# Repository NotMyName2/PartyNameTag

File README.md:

# PartyNameTag

Remember the nasty sticky paper name tags probably used at parties? Never been to any party, so I do not. Anyway, once I figure out how to put this thingy on a shirt, it can be used as a name tag.

The device can display any reasonably long message consisting of the characters in the English alphabet sent by Bluetooth from any smartphone(tested only on android). The text shifts in the same way like a "breaking news" row in the news.

In the future, I might add more functionality:

 	 *display a hard-coded message after a certain period of inactivity
        (You can ask for a girl's number this way :O )

  	*display random noise(partially done)

  	*up- and down-shifting

  	*finish the character lookup table

  	*implement the LED indicator for low battery

  	*display special emoji or animations

The thingy is based on Arduino Pro Mini, an AT09 Bluetooth module, a TC4056 Li-ion charger module, an old phone battery, 74HC595 shift registers, a DC-DC 5V voltage supply and many unipolar transistors.

The microcontroller can be easily reprogrammed using the Arduino IDE and a USB to Serial converter.

The custom PCB is in the "DivineMessengerBoard" directory. The smallest track width is 0.4mm and the smallest clearance is 0.2mm and is meant to be manufactured professionally (DIY drill or UV would probably bring frustration)

See the video at https://youtu.be/IolG6l6WMoY

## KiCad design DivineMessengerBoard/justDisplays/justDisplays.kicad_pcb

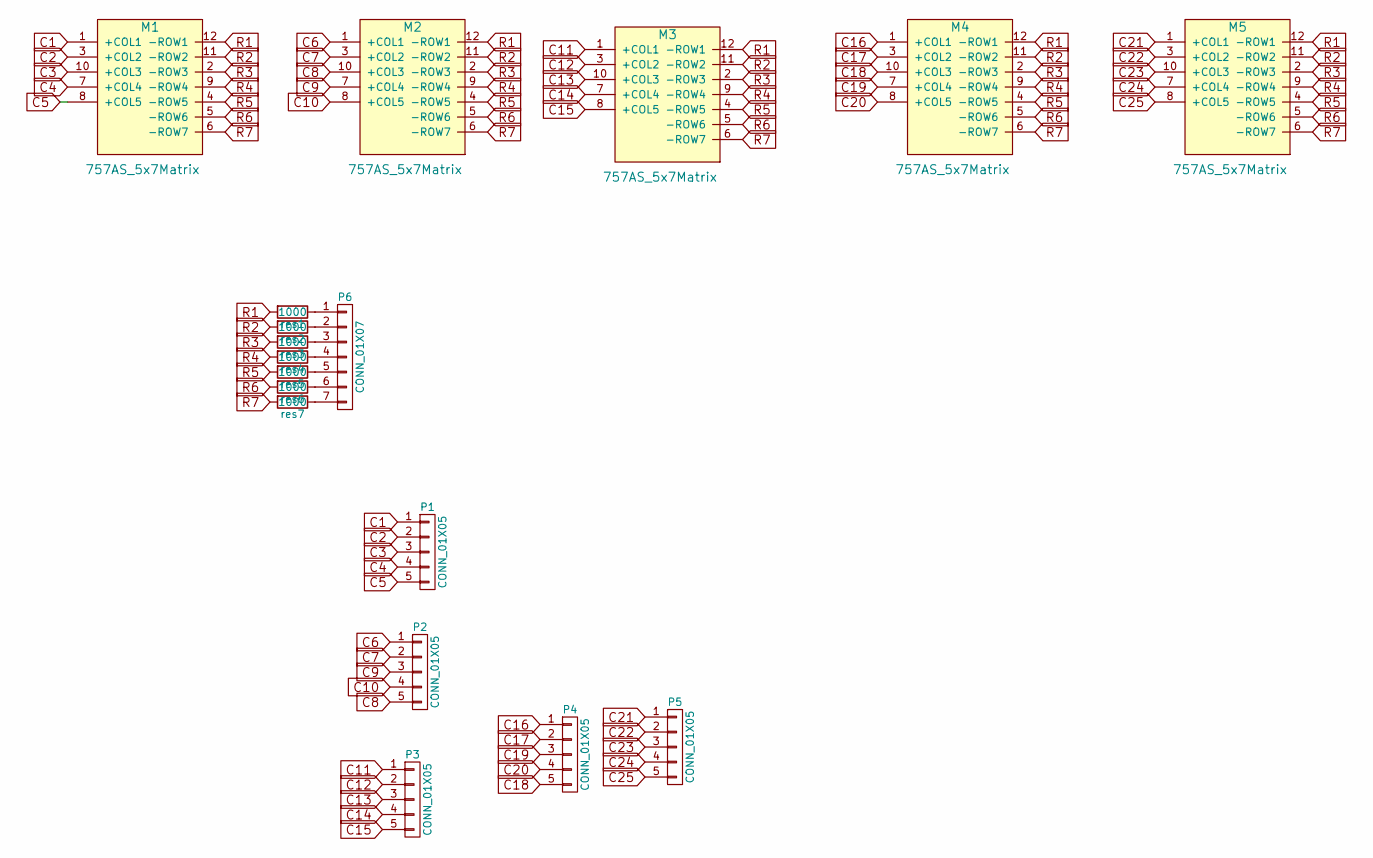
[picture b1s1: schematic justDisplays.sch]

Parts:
M1, M2, M3, M4, M5: 757AS_5x7Matrix; 757-5x7Matrix-socket
P1, P2, P3, P4, P5: CONN_01X05; NonRetardHeader1x5
P6: CONN_01X07; NonRetardHeader1x7
res1, res2, res3, res4, res5, res6, res7: 1000; R_1206_HandSoldering

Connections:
C1: M1.1 (+COL1), P1.1
C2: M1.3 (+COL2), P1.2
C3: M1.10 (+COL3), P1.3
C4: M1.7 (+COL4), P1.4
C5: M1.8 (+COL5), P1.5
C6: M2.1 (+COL1), P2.1
C7: M2.3 (+COL2), P2.2
C8: M2.10 (+COL3), P2.5
C9: M2.7 (+COL4), P2.3
C10: M2.8 (+COL5), P2.4
C11: M3.1 (+COL1), P3.1
C12: M3.3 (+COL2), P3.2
C13: M3.10 (+COL3), P3.3
C14: M3.7 (+COL4), P3.4
C15: M3.8 (+COL5), P3.5
C16: M4.1 (+COL1), P4.1
C17: M4.3 (+COL2), P4.2
C18: M4.10 (+COL3), P4.5
C19: M4.7 (+COL4), P4.3
C20: M4.8 (+COL5), P4.4
C21: M5.1 (+COL1), P5.1
C22: M5.3 (+COL2), P5.2
C23: M5.10 (+COL3), P5.3
C24: M5.7 (+COL4), P5.4
C25: M5.8 (+COL5), P5.5
unnamed: P6.1, res1.1
unnamed: P6.2, res2.1
unnamed: P6.3, res3.1
unnamed: P6.4, res4.1
unnamed: P6.5, res5.1
unnamed: P6.6, res6.1
unnamed: P6.7, res7.1
R1: M1.12 (-ROW1), M2.12 (-ROW1), M3.12 (-ROW1), M4.12 (-ROW1), M5.12 (-ROW1), res1.2
R2: M1.11 (-ROW2), M2.11 (-ROW2), M3.11 (-ROW2), M4.11 (-ROW2), M5.11 (-ROW2), res2.2
R3: M1.2 (-ROW3), M2.2 (-ROW3), M3.2 (-ROW3), M4.2 (-ROW3), M5.2 (-ROW3), res3.2
R4: M1.9 (-ROW4), M2.9 (-ROW4), M3.9 (-ROW4), M4.9 (-ROW4), M5.9 (-ROW4), res4.2
R5: M1.4 (-ROW5), M2.4 (-ROW5), M3.4 (-ROW5), M4.4 (-ROW5), M5.4 (-ROW5), res5.2
R6: M1.5 (-ROW6), M2.5 (-ROW6), M3.5 (-ROW6), M4.5 (-ROW6), M5.5 (-ROW6), res6.2
R7: M1.6 (-ROW7), M2.6 (-ROW7), M3.6 (-ROW7), M4.6 (-ROW7), M5.6 (-ROW7), res7.2

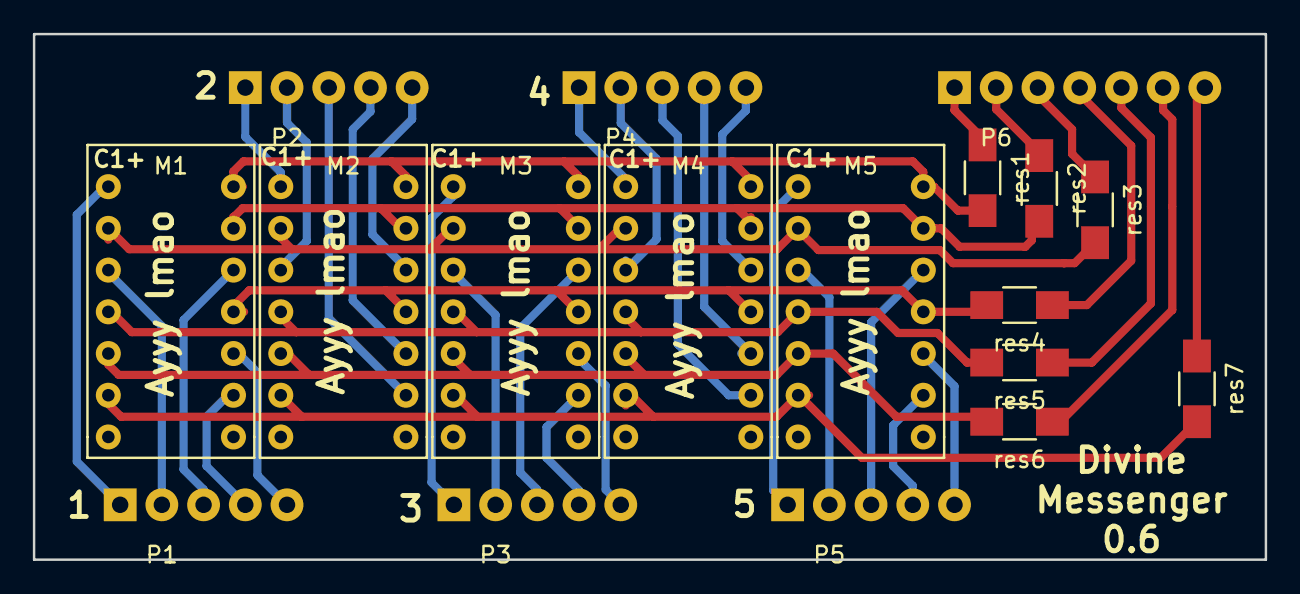
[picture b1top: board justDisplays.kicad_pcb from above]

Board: 2 copper layers, 75.0 x 32.0 mm, 18 parts (0 on the bottom side), 39 nets.

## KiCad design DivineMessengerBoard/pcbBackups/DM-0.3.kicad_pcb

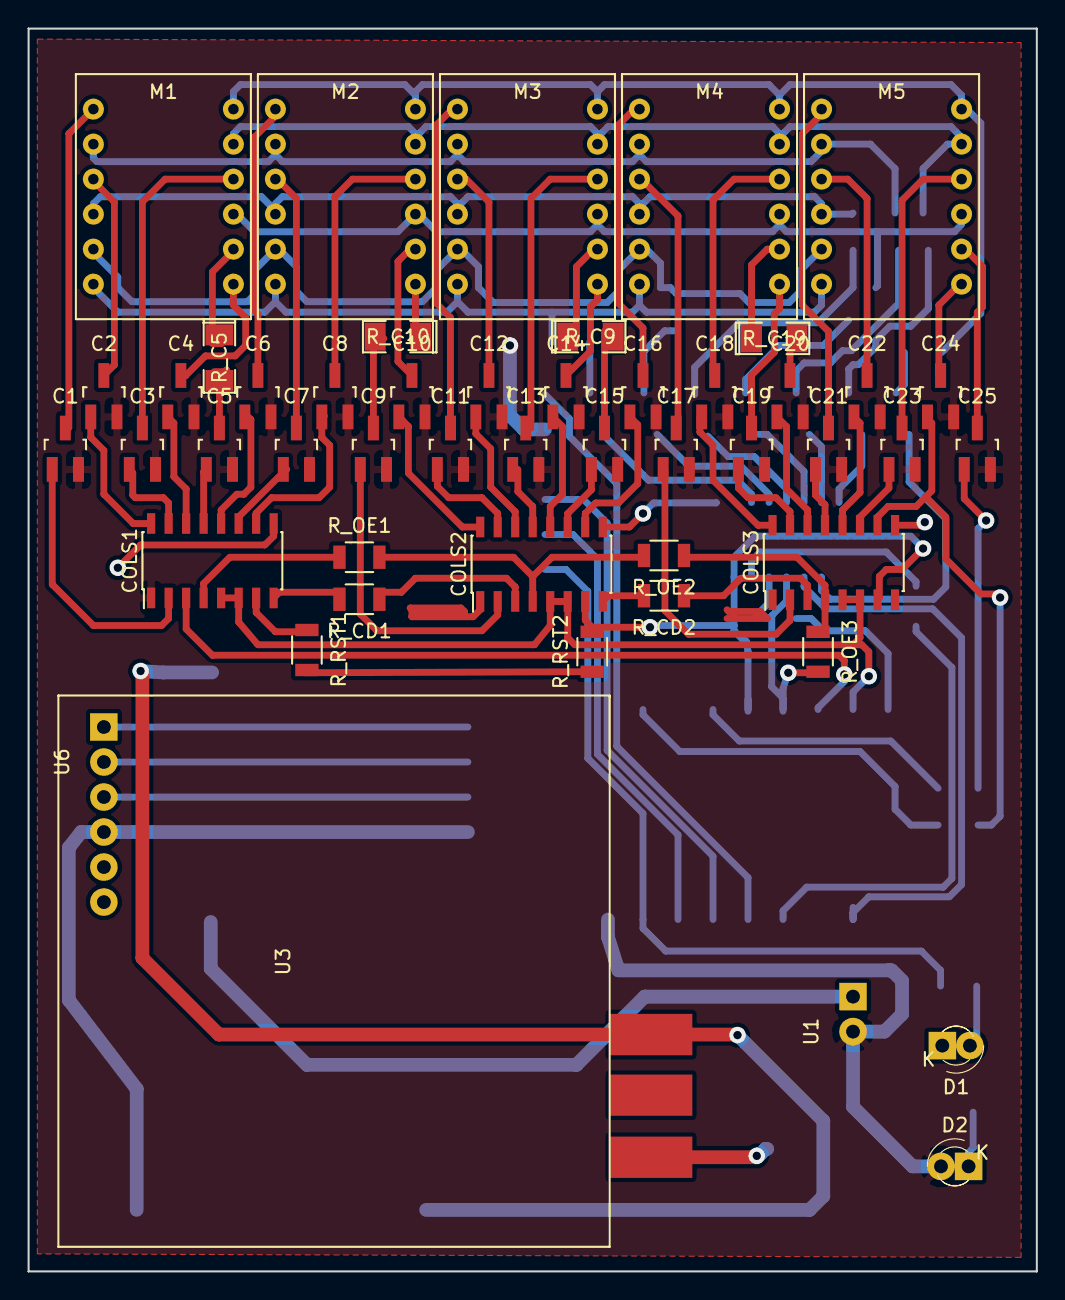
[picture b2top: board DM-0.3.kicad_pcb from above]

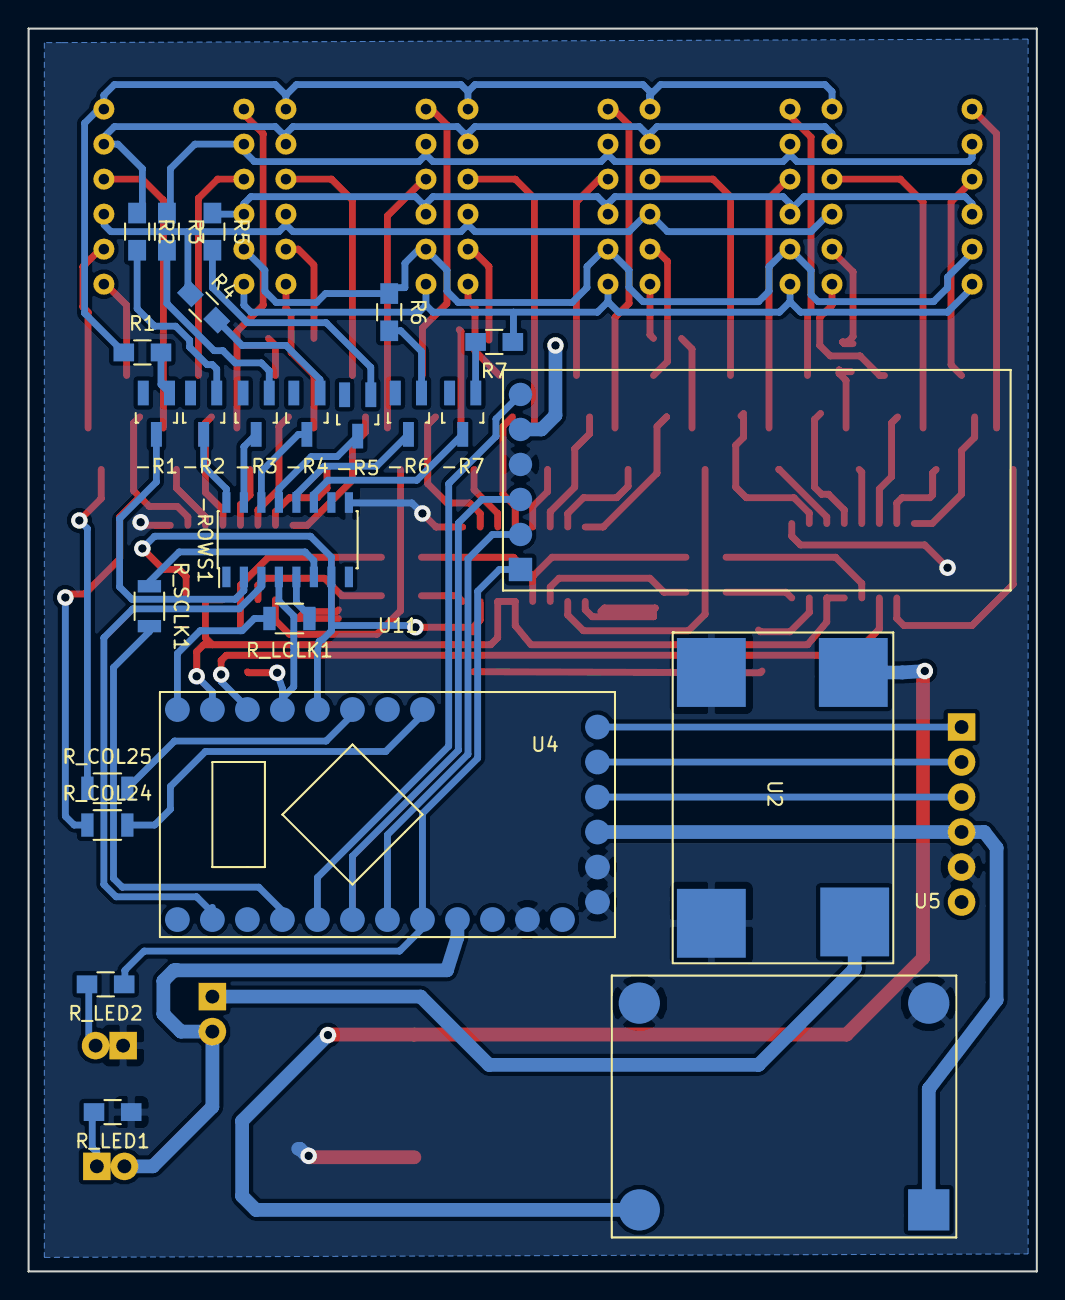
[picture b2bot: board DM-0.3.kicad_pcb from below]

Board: 2 copper layers, 73.2 x 90.2 mm, 74 parts (25 on the bottom side), 109 nets.

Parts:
-R1, -R2, -R3, -R4, -R5, -R6, -R7: Q_NMOS_DSG; SOT-23_Handsoldering
-ROWS1: 74HC595-F; SOIC-16_3.9x9.9mm_Pitch1.27mm
C1, C2, C3, C4, C5, C6, C7, C8, C9, C10, C11, C12, C13, C14, C15, C16, C17, C18, C19, C20, C21, C22, C23, C24, C25: Q_PMOS_GDS; SOT-23_Handsoldering
COLS1, COLS2, COLS3: 74HC595-F; SOIC-16_3.9x9.9mm_Pitch1.27mm
D1, D2: Led_Small; LED-3MM
M1, M2, M3, M4, M5: 757AS_5x7Matrix; 757-5x7Matrix
R1, R2, R3, R4, R5, R6, R7: 220; R_0805_HandSoldering
R_C5, R_C9, R_C10, R_C19: 0; SMD-1206_Pol
R_CD1, R_CD2: 0; R_1206
R_COL24, R_COL25: 0; R_1206
R_LCLK1: 0; R_1206
R_LED1, R_LED2: 220; R_0805_HandSoldering
R_OE1, R_OE2, R_OE3: 0; R_1206
R_RST1, R_RST2: 0; R_1206
R_SCLK1: 0; R_1206
U1: NonRetardHeader1x2
U2: DC-DC
U3: OldBat; DC-DC
U4: ArProMin; ProMiniSMDNoWeirdAndRxTxPins
U5: Li-Ion_Charger; Li-Ion-charger2-SMD
U6: NonRetardHeader; NonRetardHeader1x6
U11: BTModule; BtModuleSMD

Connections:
5V: C1.2, C2.2, C3.2, C4.2, C5.2, C6.2, C7.2, C8.2, C9.2, C10.2, C11.2, C12.2, C13.2, C14.2, C15.2, C16.2, C17.2, C18.2, C19.2, C20.2, C21.2, C22.2, C23.2, C24.2, C25.2, COLS1.1, D2.2, U1.2, U4.24, U11.5
BAT+: U2.1, U3.1, U5.4
BTIN: U4.22, U11.2
BTOUT: U4.21, U11.3
BT_CON: R_LED2.1, U4.23, U11.1
BT_EN: U4.20, U11.6
C1: C1.3, M1.1
C2: C2.3, M1.3
C3: C3.3, M1.10
C4: C4.3, M1.7
C5: C5.3, R_C5.2
C6: C6.3, M2.1
C7: C7.3, M2.3
C8: C8.3, M2.10
C9: C9.3, R_C10.2
C10: C10.3, M2.8
C11: C11.3, M3.1
C12: C12.3, M3.3
C13: C13.3, M3.10
C14: C14.3, M3.7
C15: C15.3, R_C9.2
C16: C16.3, M4.1
C17: C17.3, M4.3
C18: C18.3, M4.10
C19: C19.3, M4.7
C20: C20.3, R_C19.2
C21: C21.3, M5.1
C22: C22.3, M5.3
C23: C23.3, M5.10
C24: C24.3, M5.7
C25: C25.3, M5.8
CHRGR: U4.30, U5.1, U6.4
COL1: C1.1, COLS1.2
COL2: C2.1, COLS1.16
COL3: C3.1, COLS1.15
COL4: C4.1, COLS1.14
COL5: C5.1, COLS1.13
COL6: C6.1, COLS1.12
COL7: C7.1, COLS1.11
COL8: C8.1, COLS1.10
COL9: C9.1, COLS2.2
COL10: C10.1, COLS2.16
COL11: C11.1, COLS2.15
COL12: C12.1, COLS2.14
COL13: C13.1, COLS2.13
COL14: C14.1, COLS2.12
COL15: C15.1, COLS2.11
COL16: C16.1, COLS2.10
COL17: C17.1, COLS3.2
COL18: C18.1, COLS3.16
COL19: C19.1, COLS3.15
COL20: C20.1, COLS3.14
COL21: C21.1, COLS3.13
COL22: C22.1, COLS3.12
COL23: C23.1, COLS3.11
COL24: C24.1, COLS3.10, R_COL24.1
COL25: C25.1, R_COL25.1
ColClk: COLS1.5, COLS1.6, COLS2.5, COLS2.6, COLS3.5, COLS3.6, U4.11
ColIn: COLS1.3, U4.10
GND: -ROWS1.9, COLS1.9, COLS2.9, COLS3.9, D1.1, R_LED1.1, U2.2, U2.3, U3.3, U4.26, U4.28, U4.29, U5.2, U5.3, U6.5, U11.4
unnamed: -R1.1, R1.2
unnamed: -R2.1, R2.2
unnamed: -R3.1, R3.2
unnamed: -R4.1, R4.2
unnamed: -R5.1, R5.2
unnamed: -R6.1, R6.2
unnamed: -R7.1, R7.2
unnamed: -ROWS1.5, R_LCLK1.1
unnamed: -ROWS1.6, R_SCLK1.1
unnamed: COLS1.4, R_OE1.1
unnamed: COLS1.7, R_RST1.1
unnamed: COLS1.8, R_CD1.2
unnamed: COLS2.3, R_CD1.1
unnamed: COLS2.4, R_OE1.2, R_OE2.2
unnamed: COLS2.8, R_CD2.2
unnamed: COLS3.3, R_CD2.1
unnamed: COLS3.4, R_OE2.1, R_OE3.1
unnamed: D1.2, R_LED2.2
unnamed: D2.1, R_LED1.2
unnamed: M1.8, R_C5.1
unnamed: M2.7, R_C10.1
unnamed: M3.8, R_C9.1
unnamed: M4.8, R_C19.1
unnamed: R_COL24.2, U4.5
unnamed: R_COL25.2, U4.7
unnamed: R_RST1.2, R_RST2.1
unnamed: U4.33, U6.1
unnamed: U4.31, U6.3
unnamed: U4.32, U6.2
OE: -ROWS1.4, R_OE3.2, U4.9
Pow: U1.1, U2.4
R1: M1.12, M2.12, M3.12, M4.12, M5.12, R1.1
R2: M1.11, M2.11, M3.11, M4.11, M5.11, R2.1
R3: M1.2, M2.2, M3.2, M4.2, M5.2, R3.1
R4: M1.9, M2.9, M3.9, M4.9, M5.9, R4.1
R5: M1.4, M2.4, M3.4, M4.4, M5.4, R5.1
R6: M1.5, M2.5, M3.5, M4.5, M5.5, R6.1
R7: M1.6, M2.6, M3.6, M4.6, M5.6, R7.1
ROW1: -R1.3, -ROWS1.2
ROW2: -R2.3, -ROWS1.16
ROW3: -R3.3, -ROWS1.15
ROW4: -R4.3, -ROWS1.14
ROW5: -R5.3, -ROWS1.13
ROW6: -R6.3, -ROWS1.12
ROW7: -R7.3, -ROWS1.11
RST: -ROWS1.7, COLS2.7, COLS3.7, R_RST2.2, U4.8
RowIn: -ROWS1.3, U4.17
RowLClk: R_LCLK1.2, U4.12
RowSClk: R_SCLK1.2, U4.19

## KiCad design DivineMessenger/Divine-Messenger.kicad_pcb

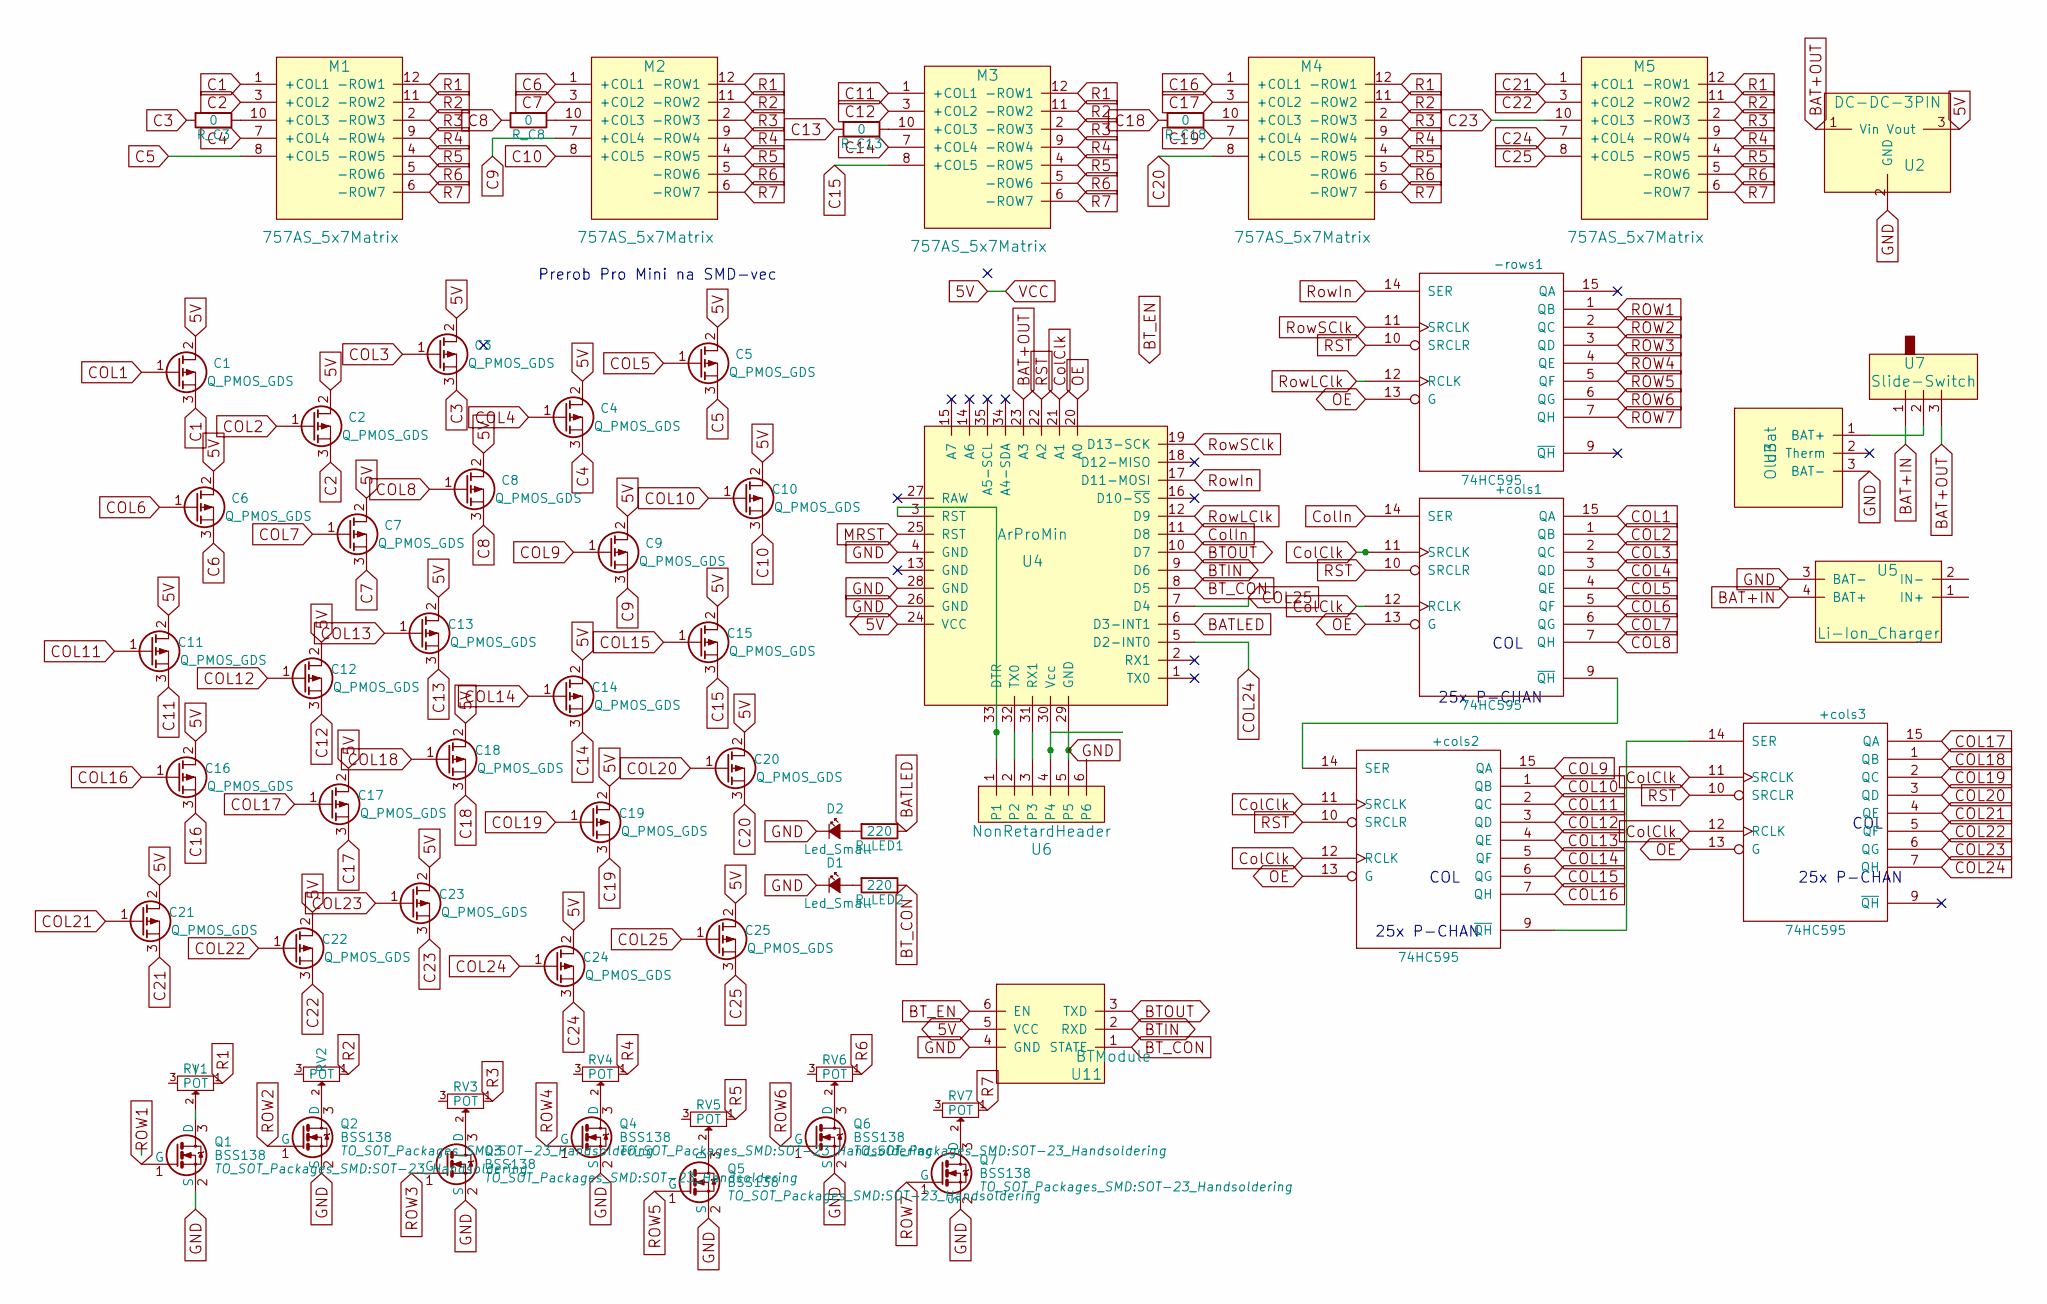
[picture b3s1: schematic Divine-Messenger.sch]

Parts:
+cols1, +cols2, +cols3: 74HC595; SOIC-16_3.9x9.9mm_Pitch1.27mm
-rows1: 74HC595; SOIC-16_3.9x9.9mm_Pitch1.27mm
C1, C2, C3, C4, C5, C6, C7, C8, C9, C10, C11, C12, C13, C14, C15, C16, C17, C18, C19, C20, C21, C22, C23, C24, C25: Q_PMOS_GDS; SOT-23_Handsoldering
D1, D2: Led_Small; LED-3MM
M1, M2, M3, M4, M5: 757AS_5x7Matrix; 757-5x7Matrix
Q1, Q2, Q3, Q4, Q5, Q6, Q7: BSS138; SOT-23_Handsoldering
RV1, RV2, RV3, RV4, RV5, RV6, RV7: POT; SMD-Trimm
R_C3, R_C8, R_C13, R_C18: 0; R_1206_HandSoldering
R_LED1, R_LED2: 220; R_0805_HandSoldering
U2: DC-DC-3PIN; NonRetardHeader1x3
U3: OldBat; oldBatTHT
U4: ArProMin; ProMiniSMDNoWeirdAndRxTxPinsLongPads
U5: Li-Ion_Charger; Li-Ion-charger1-SMD-LongPads
U6: NonRetardHeader; NonRetardHeader1x6
U7: Slide-Switch
U11: BTModule; BtModuleSMDLongPads

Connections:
5V: -rows1.16 (VCC), C1.2 (D), C2.2 (D), C3.2 (D), C4.2 (D), C5.2 (D), C6.2 (D), C7.2 (D), C8.2 (D), C9.2 (D), C10.2 (D), C11.2 (D), C12.2 (D), C13.2 (D), C14.2 (D), C15.2 (D), C16.2 (D), C17.2 (D), C18.2 (D), C19.2 (D), C20.2 (D), C21.2 (D), C22.2 (D), C23.2 (D), C24.2 (D), C25.2 (D), U2.3 (Vout), U4.24 (VCC), U11.5 (VCC); also elsewhere on the board
BAT+IN: U5.4 (BAT+), U7.1
BAT+OUT: U2.1 (Vin), U4.23 (A3), U7.3
BATLED: R_LED1.1, U4.6 (D3-INT1)
BTIN: U4.9 (D6), U11.2 (RXD)
BTOUT: U4.10 (D7), U11.3 (TXD)
BT_CON: R_LED2.1, U4.8 (D5), U11.1 (STATE)
C1: C1.3 (S), M1.1 (+COL1)
C2: C2.3 (S), M1.3 (+COL2)
C3: C3.3 (S), R_C3.2
C4: C4.3 (S), M1.7 (+COL4)
C5: C5.3 (S), M1.8 (+COL5)
C6: C6.3 (S), M2.1 (+COL1)
C7: C7.3 (S), M2.3 (+COL2)
C8: C8.3 (S), R_C8.2
C9: C9.3 (S), M2.7 (+COL4)
C10: C10.3 (S), M2.8 (+COL5)
C11: C11.3 (S), M3.1 (+COL1)
C12: C12.3 (S), M3.3 (+COL2)
C13: C13.3 (S), R_C13.2
C14: C14.3 (S), M3.7 (+COL4)
C15: C15.3 (S), M3.8 (+COL5)
C16: C16.3 (S), M4.1 (+COL1)
C17: C17.3 (S), M4.3 (+COL2)
C18: C18.3 (S), R_C18.2
C19: C19.3 (S), M4.7 (+COL4)
C20: C20.3 (S), M4.8 (+COL5)
C21: C21.3 (S), M5.1 (+COL1)
C22: C22.3 (S), M5.3 (+COL2)
C23: C23.3 (S), M5.10 (+COL3)
C24: C24.3 (S), M5.7 (+COL4)
C25: C25.3 (S), M5.8 (+COL5)
COL1: +cols1.15 (QA), C1.1 (G); also elsewhere on the board
COL2: +cols1.1 (QB), C2.1 (G); also elsewhere on the board
COL3: +cols1.2 (QC), C3.1 (G); also elsewhere on the board
COL4: +cols1.3 (QD), C4.1 (G); also elsewhere on the board
COL5: +cols1.4 (QE), C5.1 (G); also elsewhere on the board
COL6: +cols1.5 (QF), C6.1 (G); also elsewhere on the board
COL7: +cols1.6 (QG), C7.1 (G); also elsewhere on the board
COL8: +cols1.7 (QH), C8.1 (G); also elsewhere on the board
COL9: +cols2.15 (QA), C9.1 (G); also elsewhere on the board
COL10: +cols2.1 (QB), C10.1 (G); also elsewhere on the board
COL11: +cols2.2 (QC), C11.1 (G); also elsewhere on the board
COL12: +cols2.3 (QD), C12.1 (G); also elsewhere on the board
COL13: +cols2.4 (QE), C13.1 (G); also elsewhere on the board
COL14: +cols2.5 (QF), C14.1 (G); also elsewhere on the board
COL15: +cols2.6 (QG), C15.1 (G); also elsewhere on the board
COL16: +cols2.7 (QH), C16.1 (G); also elsewhere on the board
COL17: +cols3.15 (QA), C17.1 (G); also elsewhere on the board
COL18: +cols3.1 (QB), C18.1 (G); also elsewhere on the board
COL19: +cols3.2 (QC), C19.1 (G); also elsewhere on the board
COL20: +cols3.3 (QD), C20.1 (G); also elsewhere on the board
COL21: +cols3.4 (QE), C21.1 (G); also elsewhere on the board
COL22: +cols3.5 (QF), C22.1 (G); also elsewhere on the board
COL23: +cols3.6 (QG), C23.1 (G); also elsewhere on the board
COL24: +cols3.7 (QH), C24.1 (G), U4.5 (D2-INT0); also elsewhere on the board
COL25: C25.1 (G), U4.7 (D4)
ColClk: +cols1.11 (SRCLK), +cols1.12 (RCLK), +cols2.11 (SRCLK), +cols2.12 (RCLK), +cols3.11 (SRCLK), +cols3.12 (RCLK), U4.21 (A1); also elsewhere on the board
ColIn: +cols1.14 (SER), U4.11 (D8); also elsewhere on the board
GND: -rows1.8 (GND), D1.1 (K), D2.1 (K), Q1.2 (S), Q2.2 (S), Q3.2 (S), Q4.2 (S), Q5.2 (S), Q6.2 (S), Q7.2 (S), U2.2 (GND), U3.3 (BAT-), U4.4 (GND), U4.26 (GND), U4.28 (GND), U4.29 (GND), U5.3 (BAT-), U6.5, U11.4 (GND); also elsewhere on the board
unnamed 60: +cols1.9 (~QH), +cols2.14 (SER); also elsewhere on the board
unnamed 61: +cols2.9 (~QH), +cols3.14 (SER); also elsewhere on the board
unnamed: D1.2 (A), R_LED2.2
unnamed: D2.2 (A), R_LED1.2
unnamed: M1.10 (+COL3), R_C3.1
unnamed: M2.10 (+COL3), R_C8.1
unnamed: M3.10 (+COL3), R_C13.1
unnamed: M4.10 (+COL3), R_C18.1
unnamed: Q1.3 (D), RV1.2
unnamed: Q2.3 (D), RV2.2
unnamed: Q3.3 (D), RV3.2
unnamed: Q4.3 (D), RV4.2
unnamed: Q5.3 (D), RV5.2
unnamed: Q6.3 (D), RV6.2
unnamed: Q7.3 (D), RV7.2
unnamed: U3.1 (BAT+), U7.2
unnamed: U4.3 (RST), U4.33 (DTR), U6.1
unnamed: U4.30 (Vcc), U6.4
unnamed: U4.31 (RX1), U6.3
unnamed: U4.32 (TX0), U6.2
OE: +cols1.13 (G), +cols2.13 (G), +cols3.13 (G), -rows1.13 (G), U4.20 (A0); also elsewhere on the board
R1: M1.12 (-ROW1), M2.12 (-ROW1), M3.12 (-ROW1), M4.12 (-ROW1), M5.12 (-ROW1), RV1.1
R2: M1.11 (-ROW2), M2.11 (-ROW2), M3.11 (-ROW2), M4.11 (-ROW2), M5.11 (-ROW2), RV2.1
R3: M1.2 (-ROW3), M2.2 (-ROW3), M3.2 (-ROW3), M4.2 (-ROW3), M5.2 (-ROW3), RV3.1
R4: M1.9 (-ROW4), M2.9 (-ROW4), M3.9 (-ROW4), M4.9 (-ROW4), M5.9 (-ROW4), RV4.1
R5: M1.4 (-ROW5), M2.4 (-ROW5), M3.4 (-ROW5), M4.4 (-ROW5), M5.4 (-ROW5), RV5.1
R6: M1.5 (-ROW6), M2.5 (-ROW6), M3.5 (-ROW6), M4.5 (-ROW6), M5.5 (-ROW6), RV6.1
R7: M1.6 (-ROW7), M2.6 (-ROW7), M3.6 (-ROW7), M4.6 (-ROW7), M5.6 (-ROW7), RV7.1
ROW1: -rows1.1 (QB), Q1.1 (G)
ROW2: -rows1.2 (QC), Q2.1 (G)
ROW3: -rows1.3 (QD), Q3.1 (G)
ROW4: -rows1.4 (QE), Q4.1 (G)
ROW5: -rows1.5 (QF), Q5.1 (G)
ROW6: -rows1.6 (QG), Q6.1 (G)
ROW7: -rows1.7 (QH), Q7.1 (G)
RST: +cols1.10 (SRCLR), +cols2.10 (SRCLR), +cols3.10 (SRCLR), -rows1.10 (SRCLR), U4.22 (A2); also elsewhere on the board
RowIn: -rows1.14 (SER), U4.17 (D11-MOSI)
RowLClk: -rows1.12 (RCLK), U4.12 (D9)
RowSClk: -rows1.11 (SRCLK), U4.19 (D13-SCK)

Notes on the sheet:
COL
25x P-CHAN
Prerob Pro Mini na SMD-vec

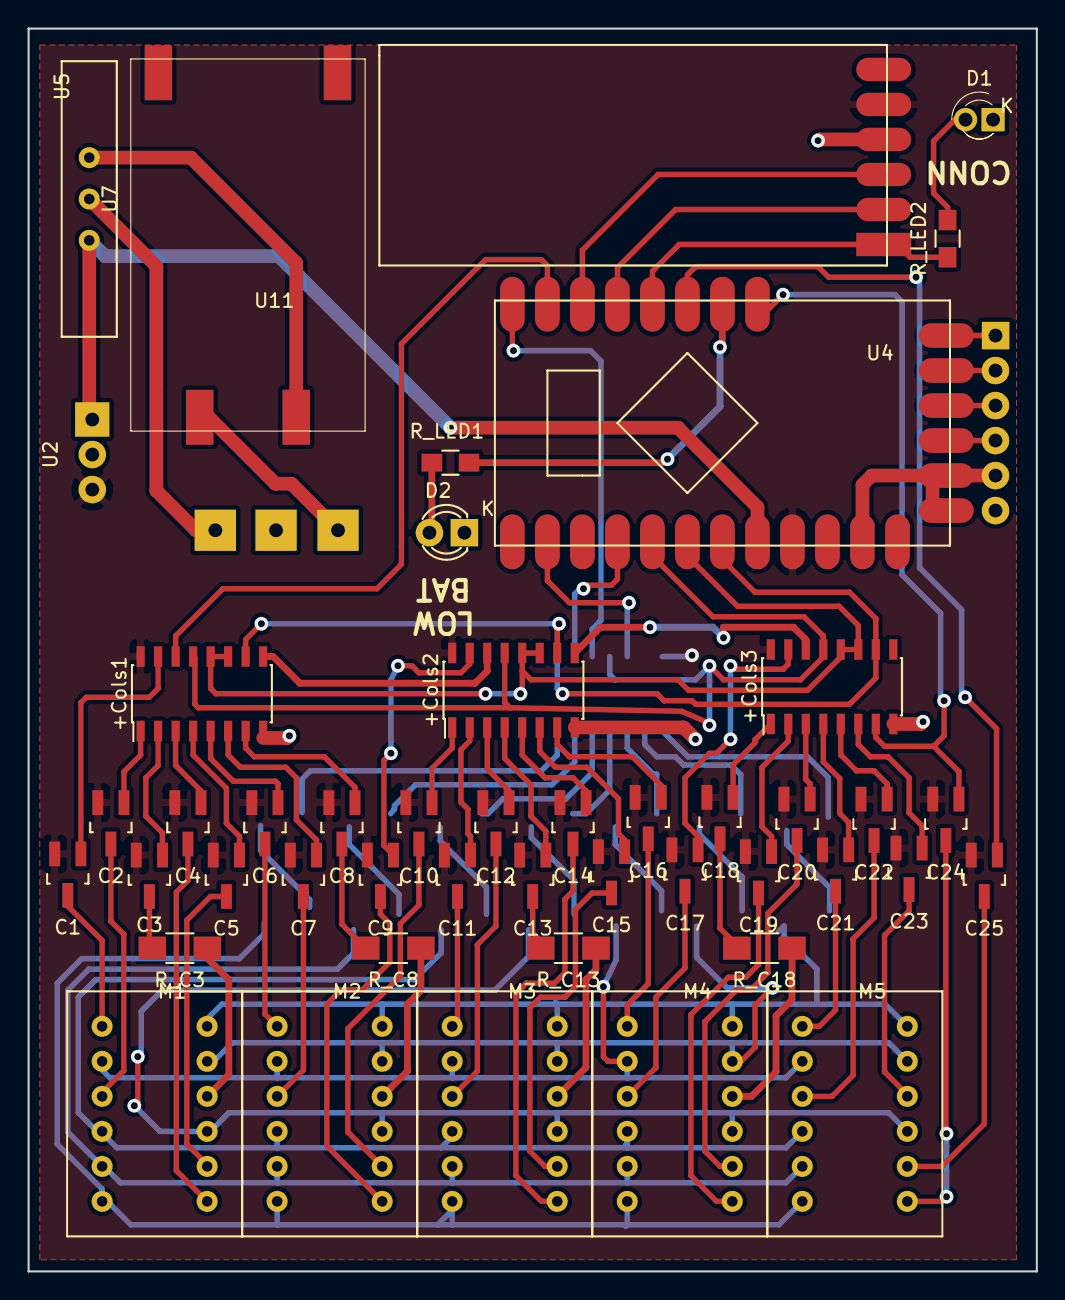
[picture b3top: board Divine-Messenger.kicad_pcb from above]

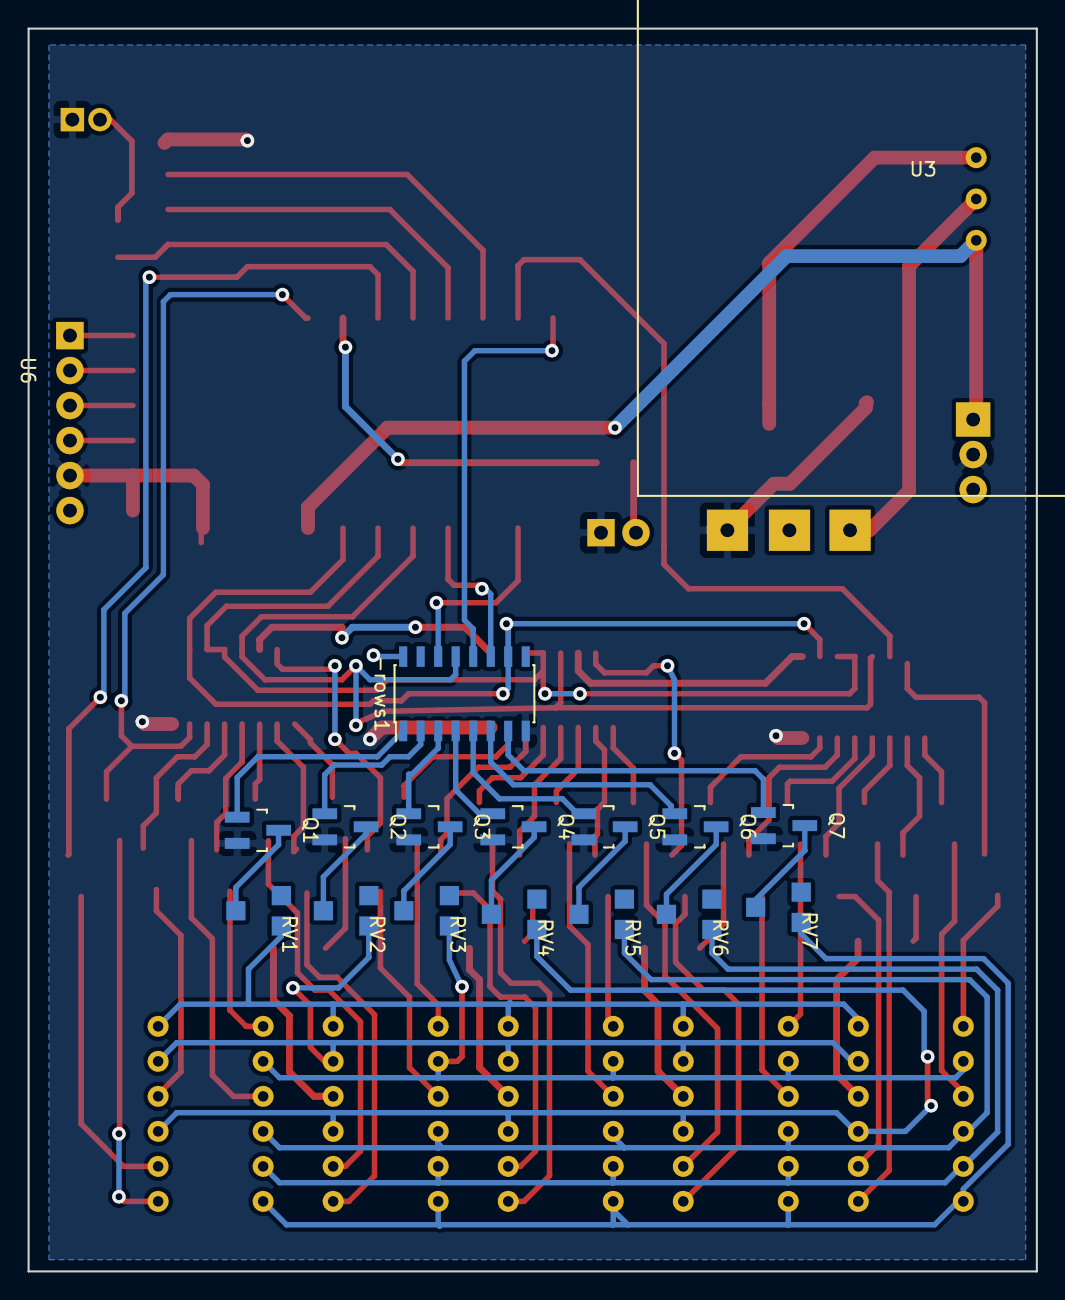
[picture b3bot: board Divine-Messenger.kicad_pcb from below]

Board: 2 copper layers, 73.2 x 90.2 mm, 63 parts (17 on the bottom side), 99 nets.

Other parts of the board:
+Cols1, +Cols2, +Cols3: 74HC595; SOIC-16_3.9x9.9mm_Pitch1.27mm

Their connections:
5V: +Cols1.16, +Cols2.16, +Cols3.16; also elsewhere on the board
COL1: +Cols1.15; also elsewhere on the board
COL2: +Cols1.1; also elsewhere on the board
COL3: +Cols1.2; also elsewhere on the board
COL4: +Cols1.3; also elsewhere on the board
COL5: +Cols1.4; also elsewhere on the board
COL6: +Cols1.5; also elsewhere on the board
COL7: +Cols1.6; also elsewhere on the board
COL8: +Cols1.7; also elsewhere on the board
COL9: +Cols2.15; also elsewhere on the board
COL10: +Cols2.1; also elsewhere on the board
COL11: +Cols2.2; also elsewhere on the board
COL12: +Cols2.3; also elsewhere on the board
COL13: +Cols2.4; also elsewhere on the board
COL14: +Cols2.5; also elsewhere on the board
COL15: +Cols2.6; also elsewhere on the board
COL16: +Cols2.7; also elsewhere on the board
COL17: +Cols3.15; also elsewhere on the board
COL18: +Cols3.1; also elsewhere on the board
COL19: +Cols3.2; also elsewhere on the board
COL20: +Cols3.3; also elsewhere on the board
COL21: +Cols3.4; also elsewhere on the board
COL22: +Cols3.5; also elsewhere on the board
COL23: +Cols3.6; also elsewhere on the board
COL24: +Cols3.7; also elsewhere on the board
ColClk: +Cols1.11, +Cols1.12, +Cols2.11, +Cols2.12, +Cols3.11, +Cols3.12; also elsewhere on the board
ColIn: +Cols1.14; also elsewhere on the board
GND: +Cols1.8, +Cols2.8, +Cols3.8; also elsewhere on the board
unnamed 60: +Cols1.9, +Cols2.14; also elsewhere on the board
unnamed 61: +Cols2.9, +Cols3.14; also elsewhere on the board
OE: +Cols1.13, +Cols2.13, +Cols3.13; also elsewhere on the board
RST: +Cols1.10, +Cols2.10, +Cols3.10; also elsewhere on the board

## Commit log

2020-01-12 Inital Commit
2020-01-14 BoardCommit
2020-01-14 :pdated Readme
